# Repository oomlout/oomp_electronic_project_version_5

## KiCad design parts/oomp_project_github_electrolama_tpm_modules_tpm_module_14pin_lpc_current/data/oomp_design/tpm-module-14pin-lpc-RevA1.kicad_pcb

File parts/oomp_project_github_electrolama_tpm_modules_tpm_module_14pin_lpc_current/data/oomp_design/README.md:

# OOMP KiCad design copy

Open `tpm-module-14pin-lpc-RevA1.kicad_pro` (or the `.kicad_pcb` / `.kicad_sch`) in KiCad. Local OOMP libraries are under `libraries/`. Original inputs are preserved in [../original/](../original/).

Only verified unchanged installed KiCad defaults were renamed. Modified, custom, unmatched and unavailable items remain unchanged. Soldering variants are never swapped during conversion. Existing pad coordinates, nets and UUIDs are preserved.

See [conversion_report.yaml](conversion_report.yaml) for every conversion and skip. Copy this directory before editing; regeneration refuses to overwrite edited design files.

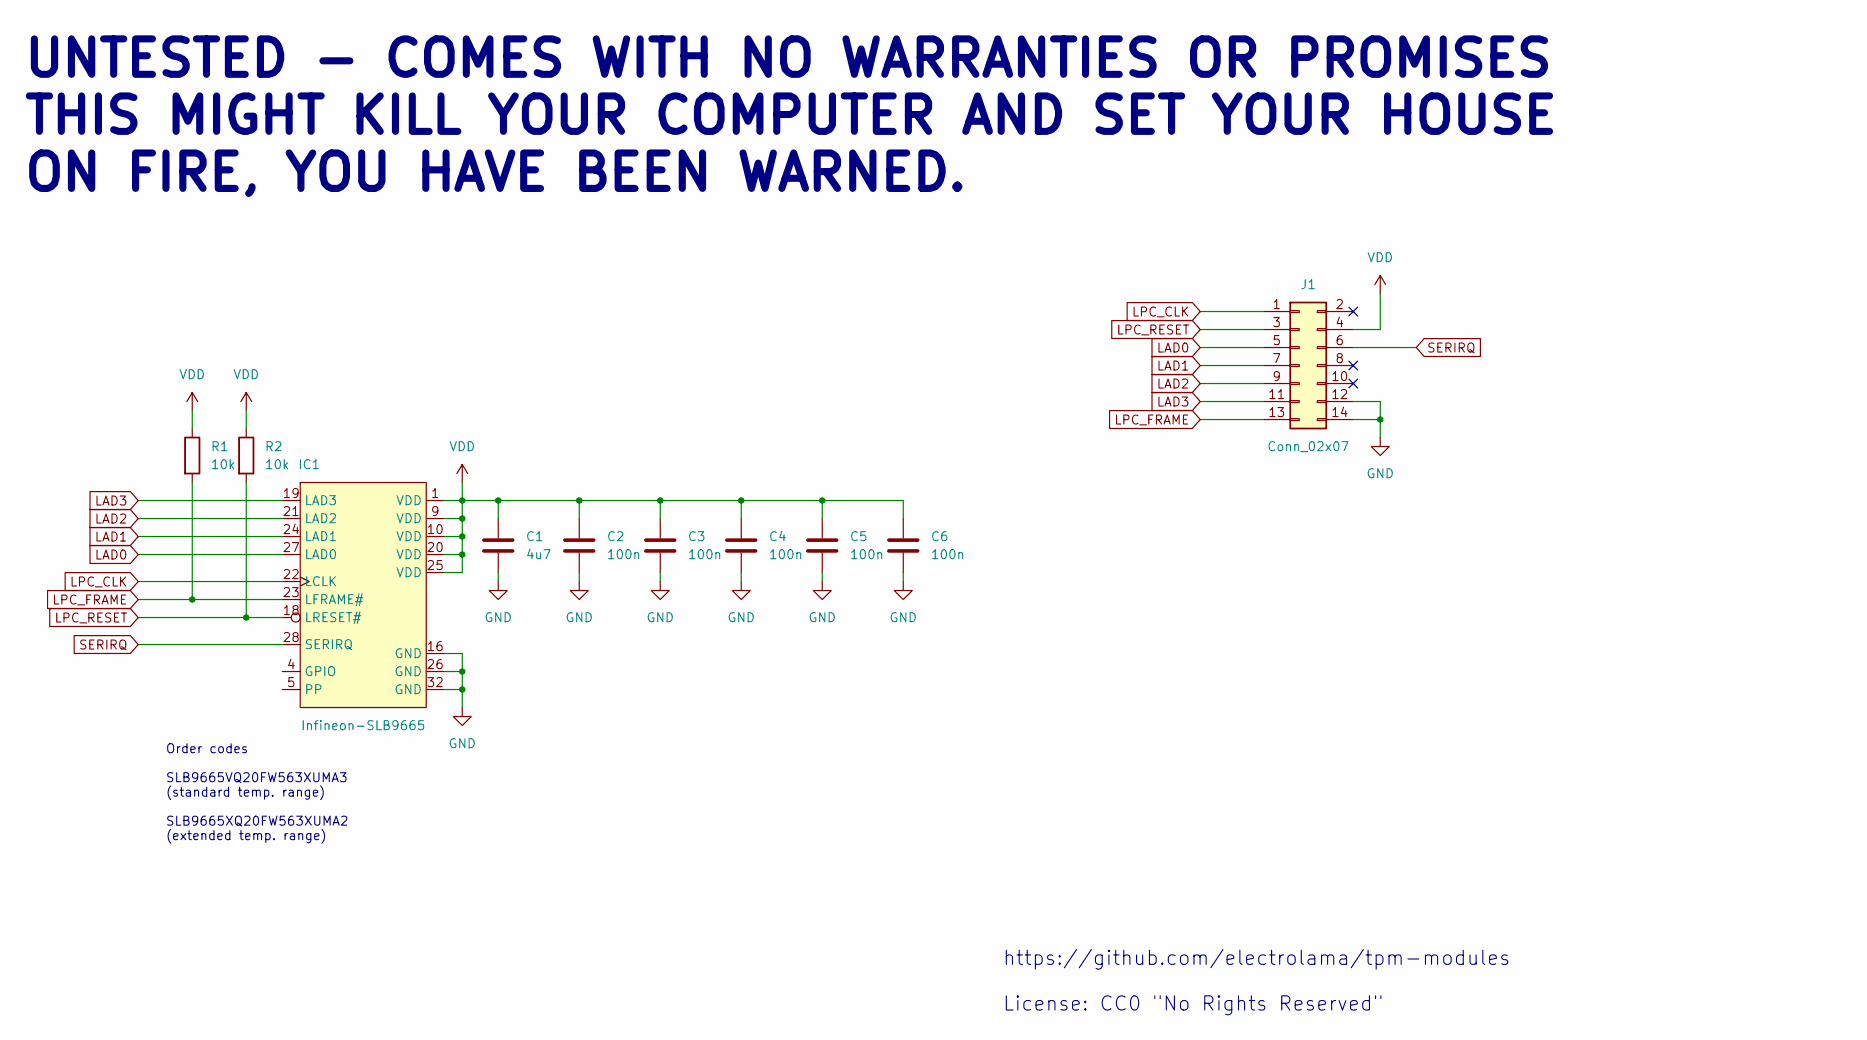
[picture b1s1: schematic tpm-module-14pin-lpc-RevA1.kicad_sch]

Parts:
C1: 4u7; C_0402_1005Metric
C2, C3, C4, C5, C6: 100n; C_0402_1005Metric
IC1: Infineon-SLB9665; QFN-32-1EP_5x5mm_P0.5mm_EP3.1x3.1mm
J1: Conn_02x07; PinSocket_2x07_P2.54mm_Horizontal
R1, R2: 10k; R_0402_1005Metric

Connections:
GND: C1.2, C2.2, C3.2, C4.2, C5.2, C6.2, IC1.16 (GND), IC1.26 (GND), IC1.32 (GND), J1.12, J1.14
LAD0: IC1.27 (LAD0), J1.5
LAD1: IC1.24 (LAD1), J1.7
LAD2: IC1.21 (LAD2), J1.9
LAD3: IC1.19 (LAD3), J1.11
LPC_CLK: IC1.22 (LCLK), J1.1
LPC_FRAME: IC1.23 (LFRAME#), J1.13, R1.2
LPC_RESET: IC1.18 (LRESET#), J1.3, R2.2
SERIRQ: IC1.28 (SERIRQ), J1.6
VDD: C1.1, C2.1, C3.1, C4.1, C5.1, C6.1, IC1.1 (VDD), IC1.9 (VDD), IC1.10 (VDD), IC1.20 (VDD), IC1.25 (VDD), J1.4, R1.1, R2.1

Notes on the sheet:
UNTESTED - COMES WITH NO WARRANTIES OR PROMISES THIS MIGHT KILL YOUR COMPUTER AND SET YOUR HOUSE ON FIRE, YOU HAVE BEEN WARNED.
Order codes SLB9665VQ20FW563XUMA3 (standard temp. range) SLB9665XQ20FW563XUMA2 (extended temp. range)
https://github.com/electrolama/tpm-modules License: CC0 "No Rights Reserved"

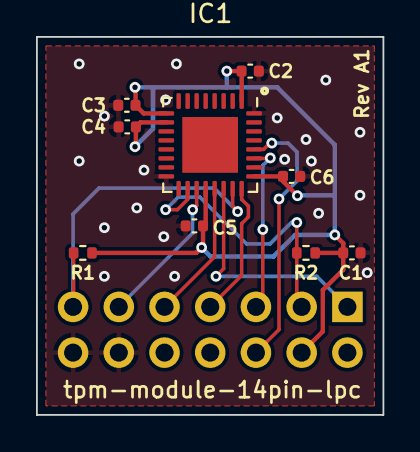
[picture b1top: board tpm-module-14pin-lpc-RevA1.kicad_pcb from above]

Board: 2 copper layers, 19.2 x 21.0 mm, 10 parts (1 on the bottom side), 10 nets.

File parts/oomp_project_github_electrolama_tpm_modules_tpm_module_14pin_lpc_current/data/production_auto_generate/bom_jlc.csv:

Comment,Designator,Footprint,LCSC Part #
100n,"C2,C3,C4,C5,C6",Capacitor_SMD:C_0402_1005Metric,C60474
10k,"R1,R2",Resistor_SMD:R_0402_1005Metric,C2906861
4u7,C1,Capacitor_SMD:C_0402_1005Metric,C368809
Conn_02x07,J1,Connector_PinSocket_2.54mm:PinSocket_2x07_P2.54mm_Horizontal,
Infineon-SLB9665,IC1,Package_DFN_QFN:QFN-32-1EP_5x5mm_P0.5mm_EP3.1x3.1mm,

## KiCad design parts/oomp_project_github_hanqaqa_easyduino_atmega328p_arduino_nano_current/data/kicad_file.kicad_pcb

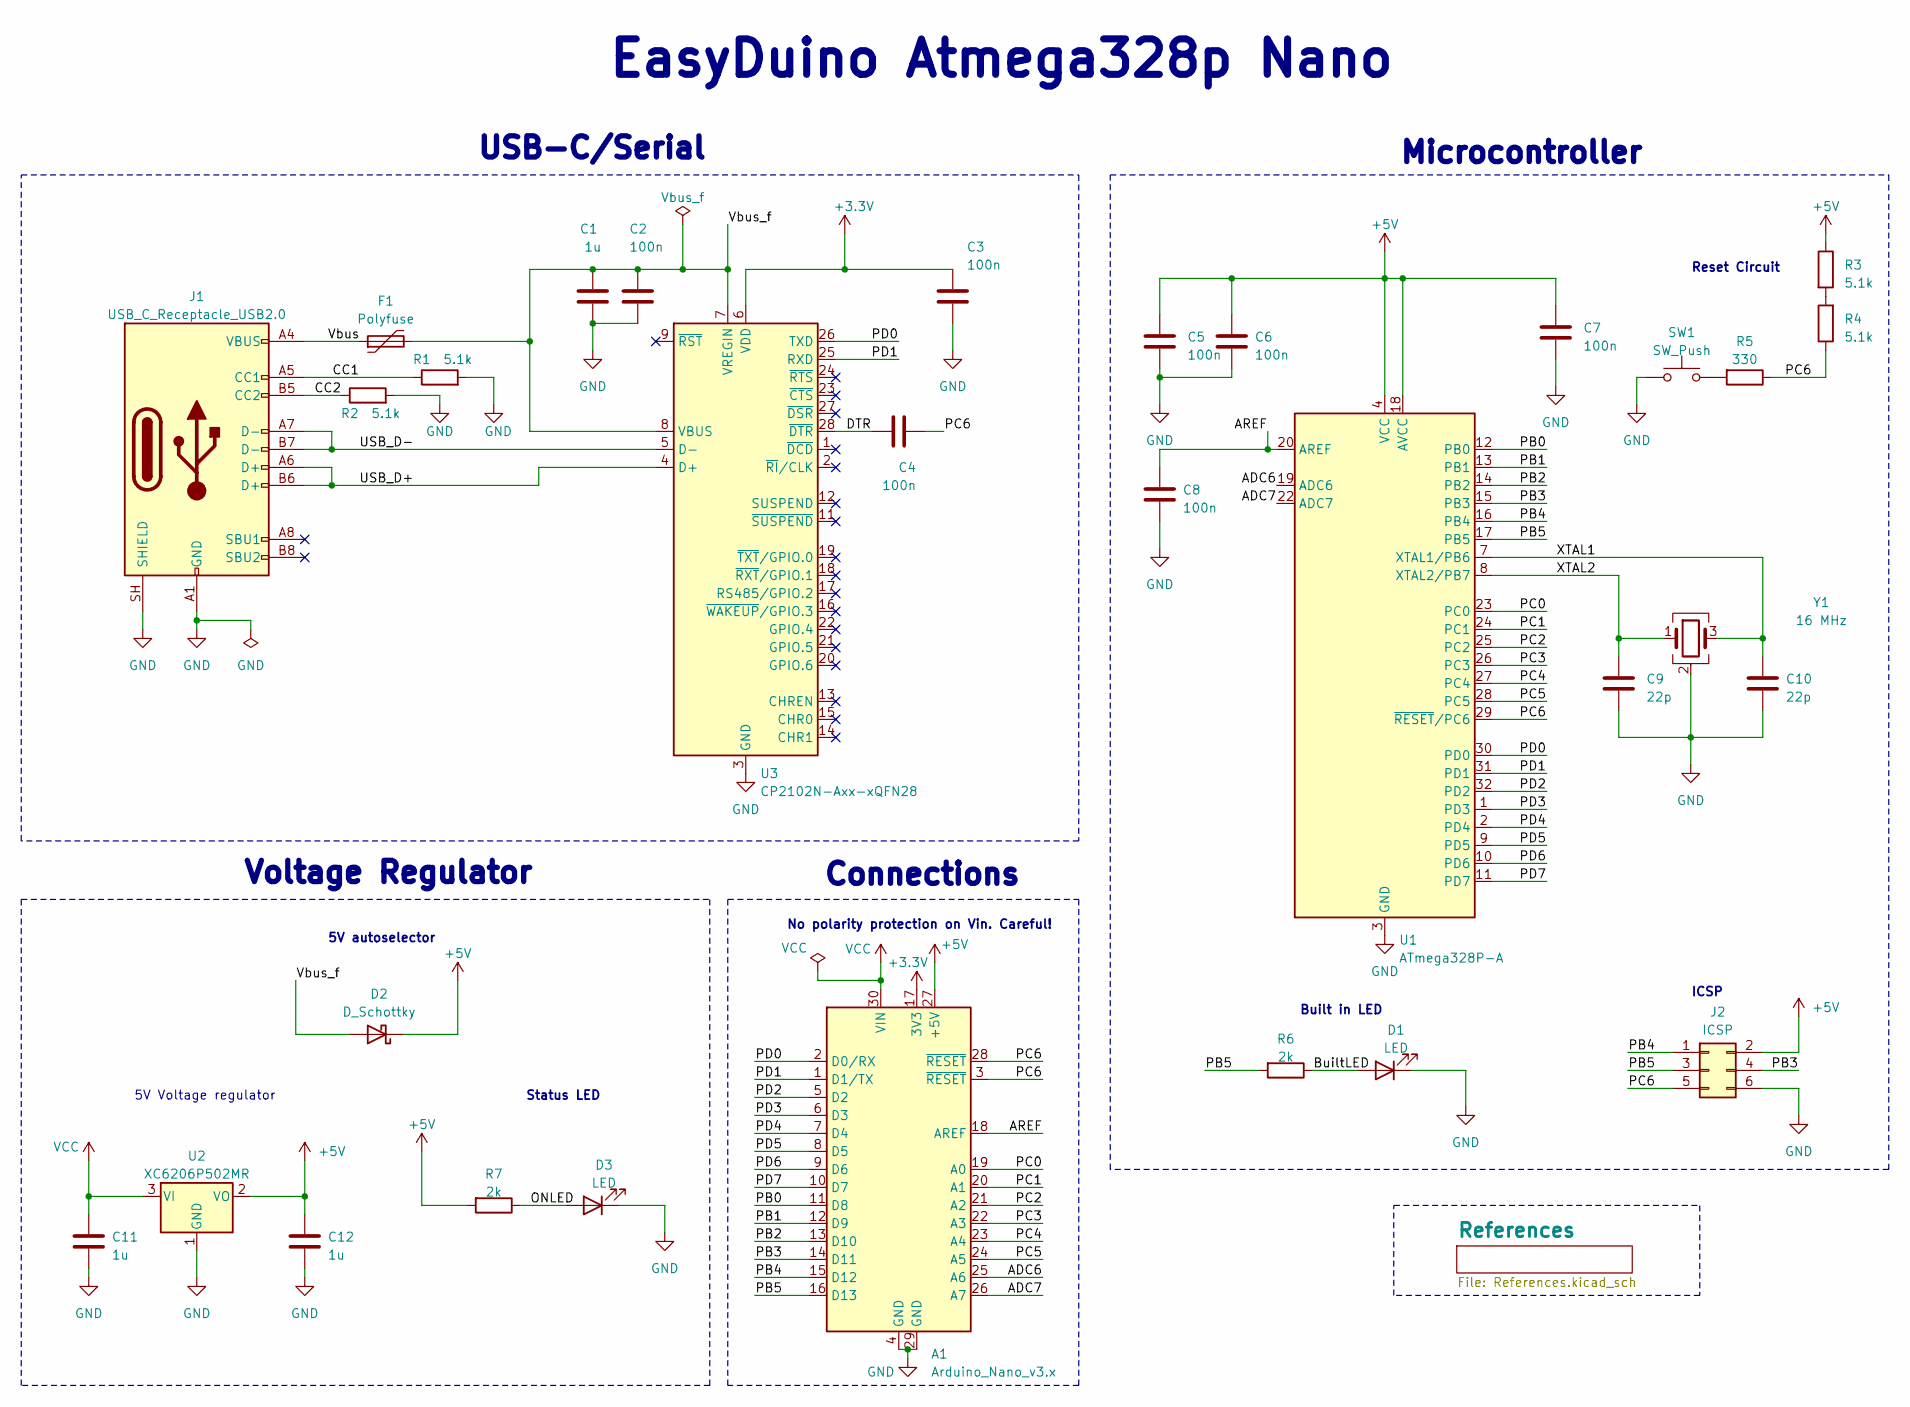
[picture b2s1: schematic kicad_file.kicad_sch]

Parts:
A1: Arduino_Nano_v3.x; Arduino_Nano_WithMountingHoles
C1, C11, C12: 1u; C_0402_1005Metric; LCSC C52923
C2, C3, C4, C5, C6, C7, C8: 100n; C_0402_1005Metric; LCSC C1525
C9, C10: 22p; C_0402_1005Metric; LCSC C1555
D1, D3: LED; LED_0402_1005Metric; LCSC C434447
D2: D_Schottky; D_0402_1005Metric; LCSC C2837790
F1: Polyfuse; Fuse_0402_1005Metric; LCSC C914087
J1: USB_C_Receptacle_USB2.0; USB_C_Receptacle_G-Switch_GT-USB-7010ASV; LCSC C2765186
J2: ICSP; PinHeader_2x03_P2.54mm_Vertical
R1, R2, R3, R4: 5.1k; R_0402_1005Metric; LCSC C25905
R5: 330; R_0402_1005Metric; LCSC C25104
R6, R7: 2k; R_0402_1005Metric; LCSC C4109
SW1: SW_Push; SW_Tactile_SPST_NO_Straight_CK_PTS636Sx25SMTRLFS; LCSC C520860
U1: ATmega328P-A; TQFP-32_7x7mm_P0.8mm; LCSC C14877
U2: XC6206P502MR; SOT-23-3; LCSC C16767
U3: CP2102N-Axx-xQFN28; QFN-28-1EP_5x5mm_P0.5mm_EP3.35x3.35mm; LCSC C6568
Y1: 16 MHz; Crystal_SMD_3225-4Pin_3.2x2.5mm; LCSC C13738

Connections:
+3.3V: A1.17 (3V3), C3.1, U3.6 (VDD)
+5V: A1.27 (+5V), C5.1, C6.1, C7.2, C12.1, D2.1 (K), J2.2, R3.1, R7.2, U1.4 (VCC), U1.6 (VCC), U1.18 (AVCC), U2.2 (VO)
/ADC6: A1.25 (A6), U1.19 (ADC6)
/ADC7: A1.26 (A7), U1.22 (ADC7)
/AREF: A1.18 (AREF), C8.1, U1.20 (AREF)
/BuiltLED: D1.2 (A), R6.1
/CC1: J1.A5 (CC1), R1.1
/CC2: J1.B5 (CC2), R2.1
/DTR: C4.1, U3.28 (~DTR)
/ONLED: D3.2 (A), R7.1
/PB0: A1.11 (D8), U1.12 (PB0)
/PB1: A1.12 (D9), U1.13 (PB1)
/PB2: A1.13 (D10), U1.14 (PB2)
/PB3: A1.14 (D11), J2.4, U1.15 (PB3)
/PB4: A1.15 (D12), J2.1, U1.16 (PB4)
/PB5: A1.16 (D13), J2.3, R6.2, U1.17 (PB5)
/PC0: A1.19 (A0), U1.23 (PC0)
/PC1: A1.20 (A1), U1.24 (PC1)
/PC2: A1.21 (A2), U1.25 (PC2)
/PC3: A1.22 (A3), U1.26 (PC3)
/PC4: A1.23 (A4), U1.27 (PC4)
/PC5: A1.24 (A5), U1.28 (PC5)
/PC6: A1.3 (~RESET), A1.28 (~RESET), C4.2, J2.5, R4.1, R5.1, U1.29 (~RESET/PC6)
/PD0: A1.2 (D0/RX), U1.30 (PD0), U3.26 (TXD)
/PD1: A1.1 (D1/TX), U1.31 (PD1), U3.25 (RXD)
/PD2: A1.5 (D2), U1.32 (PD2)
/PD3: A1.6 (D3), U1.1 (PD3)
/PD4: A1.7 (D4), U1.2 (PD4)
/PD5: A1.8 (D5), U1.9 (PD5)
/PD6: A1.9 (D6), U1.10 (PD6)
/PD7: A1.10 (D7), U1.11 (PD7)
/USB_D+: J1.A6 (D+), J1.B6 (D+), U3.4 (D+)
/USB_D-: J1.A7 (D-), J1.B7 (D-), U3.5 (D-)
/Vbus: F1.1, J1.A4 (VBUS), J1.A9 (VBUS), J1.B4 (VBUS), J1.B9 (VBUS)
/Vbus_f: C1.1, C2.1, D2.2 (A), F1.2, U3.7 (VREGIN), U3.8 (VBUS)
/XTAL1: C10.1, U1.7 (XTAL1/PB6), Y1.3
/XTAL2: C9.2, U1.8 (XTAL2/PB7), Y1.1
GND: A1.4 (GND), A1.29 (GND), C1.2, C2.2, C3.2, C5.2, C6.2, C7.1, C8.2, C9.1, C10.2, C11.2, C12.2, D1.1 (K), D3.1 (K), J1.A1 (GND), J1.A12 (GND), J1.B1 (GND), J1.B12 (GND), J1.SH (SHIELD), J2.6, R1.2, R2.2, SW1.1, U1.3 (GND), U1.5 (GND), U1.21 (GND), U2.1 (GND), U3.3 (GND), U3.29 (GND), Y1.2 (G), Y1.4 (G)
unnamed: R3.2, R4.2
unnamed: R5.2, SW1.2
VCC: A1.30 (VIN), C11.1, U2.3 (VI)

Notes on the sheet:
USB-C/Serial
Status LED
Microcontroller
Connections
ICSP
Reset Circuit
Voltage Regulator
5V autoselector
EasyDuino Atmega328p Nano
Built in LED
No polarity protection on Vin. Careful!
5V Voltage regulator

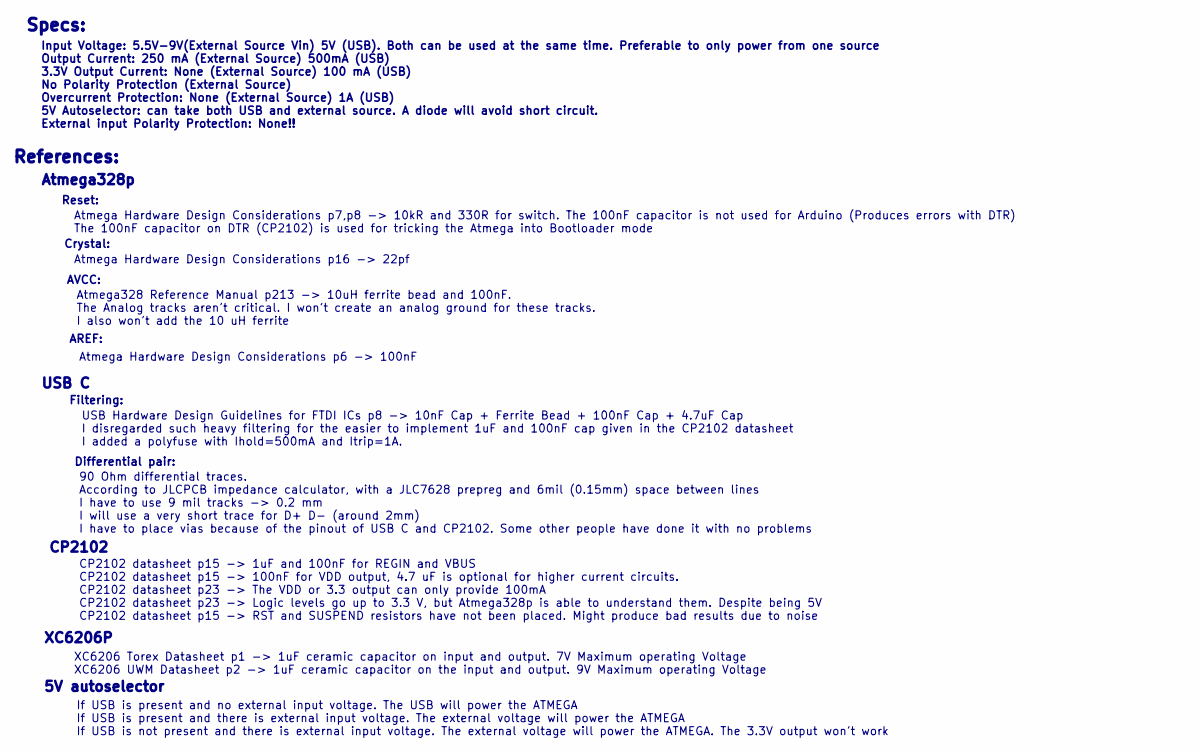
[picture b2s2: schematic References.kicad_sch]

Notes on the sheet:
AREF:
References:
Atmega328 Reference Manual p213 -> 10uH ferrite bead and 100nF. The Analog tracks aren't critical. I won't create an analog ground for these tracks. I also won't add the 10 uH ferrite
Atmega Hardware Design Considerations p7,p8 -> 10kR and 330R for switch. The 100nF capacitor is not used for Arduino (Produces errors with DTR) The 100nF capacitor on DTR (CP2102) is used for tricking the Atmega into Bootloader mode
Atmega328p
Specs:
CP2102
90 Ohm differential traces. According to JLCPCB impedance calculator, with a JLC7628 prepreg and 6mil (0.15mm) space between lines I have to use 9 mil tracks -> 0.2 mm I will use a very short trace for D+ D- (around 2mm) I have to place vias because of the pinout of USB C and CP2102. Some other peo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
5V autoselector
Filtering:
If USB is present and no external input voltage. The USB will power the ATMEGA If USB is present and there is external input voltage. The external voltage will power the ATMEGA If USB is not present and there is external input voltage. The external voltage will power the ATMEGA. The 3.3V output won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
XC6206P
Crystal:
Reset:
CP2102 datasheet p15 -> 1uF and 100nF for REGIN and VBUS CP2102 datasheet p15 -> 100nF for VDD output, 4.7 uF is optional for higher current circuits. CP2102 datasheet p23 -> The VDD or 3.3 output can only provide 100mA CP2102 datasheet p23 -> Logic levels go up to 3.3 V, but Atmega328p is able to 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
AVCC:
Atmega Hardware Design Considerations p6 -> 100nF
USB C
Differential pair:
USB Hardware Design Guidelines for FTDI ICs p8 -> 10nF Cap + Ferrite Bead + 100nF Cap + 4.7uF Cap I disregarded such heavy filtering for the easier to implement 1uF and 100nF cap given in the CP2102 datasheet I added a polyfuse with Ihold=500mA and Itrip=1A.
Atmega Hardware Design Considerations p16 -> 22pf
Input Voltage: 5.5V-9V(External Source Vin) 5V (USB). Both can be used at the same time. Preferable to only power from one source Output Current: 250 mA (External Source) 500mA (USB) 3.3V Output Current: None (External Source) 100 mA (USB) No Polarity Protection (External Source) Overcurrent Protec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
XC6206 Torex Datasheet p1 -> 1uF ceramic capacitor on input and output. 7V Maximum operating Voltage XC6206 UWM Datasheet p2 -> 1uF ceramic capacitor on the input and output. 9V Maximum operating Voltage

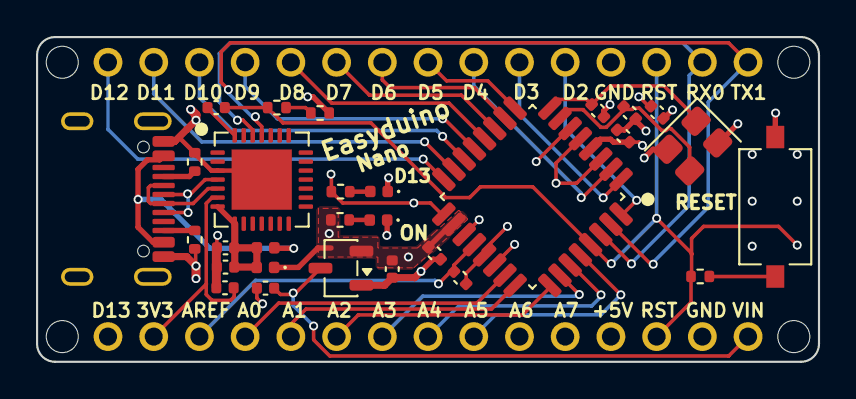
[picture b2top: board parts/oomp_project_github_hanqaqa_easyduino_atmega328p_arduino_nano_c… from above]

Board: 4 copper layers, 43.4 x 18.0 mm, 31 parts (1 on the bottom side), 41 nets.

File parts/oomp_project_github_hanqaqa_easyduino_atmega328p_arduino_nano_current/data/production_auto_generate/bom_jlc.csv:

Comment,Designator,Footprint,LCSC Part #
100n,"C2,C3,C4,C5,C6,C7,C8",Capacitor_SMD:C_0402_1005Metric,C1525
16 MHz,Y1,Crystal:Crystal_SMD_3225-4Pin_3.2x2.5mm,C13738
1u,"C1,C11,C12",Capacitor_SMD:C_0402_1005Metric,C52923
22p,"C9,C10",Capacitor_SMD:C_0402_1005Metric,C1555
2k,"R6,R7",Resistor_SMD:R_0402_1005Metric,C4109
330,R5,Resistor_SMD:R_0402_1005Metric,C25104
5.1k,"R1,R2,R3,R4",Resistor_SMD:R_0402_1005Metric,C25905
Arduino_Nano_v3.x,A1,Module:Arduino_Nano_WithMountingHoles,-
ATmega328P-A,U1,Package_QFP:TQFP-32_7x7mm_P0.8mm,C14877
CP2102N-Axx-xQFN28,U3,Package_DFN_QFN:QFN-28-1EP_5x5mm_P0.5mm_EP3.35x3.35mm,C6568
D_Schottky,D2,Diode_SMD:D_0402_1005Metric,C2837790
ICSP,J2,Connector_PinHeader_2.54mm:PinHeader_2x03_P2.54mm_Vertical,-
LED,"D1,D3",LED_SMD:LED_0402_1005Metric,C434447
Polyfuse,F1,Fuse:Fuse_0402_1005Metric,C914087
SW_Push,SW1,Button_Switch_SMD:SW_Tactile_SPST_NO_Straight_CK_PTS636Sx25SMTRLFS,C520860
USB_C_Receptacle_USB2.0,J1,Connector_USB:USB_C_Receptacle_G-Switch_GT-USB-7010ASV,C2765186
XC6206P502MR,U2,Package_TO_SOT_SMD:SOT-23-3,C16767

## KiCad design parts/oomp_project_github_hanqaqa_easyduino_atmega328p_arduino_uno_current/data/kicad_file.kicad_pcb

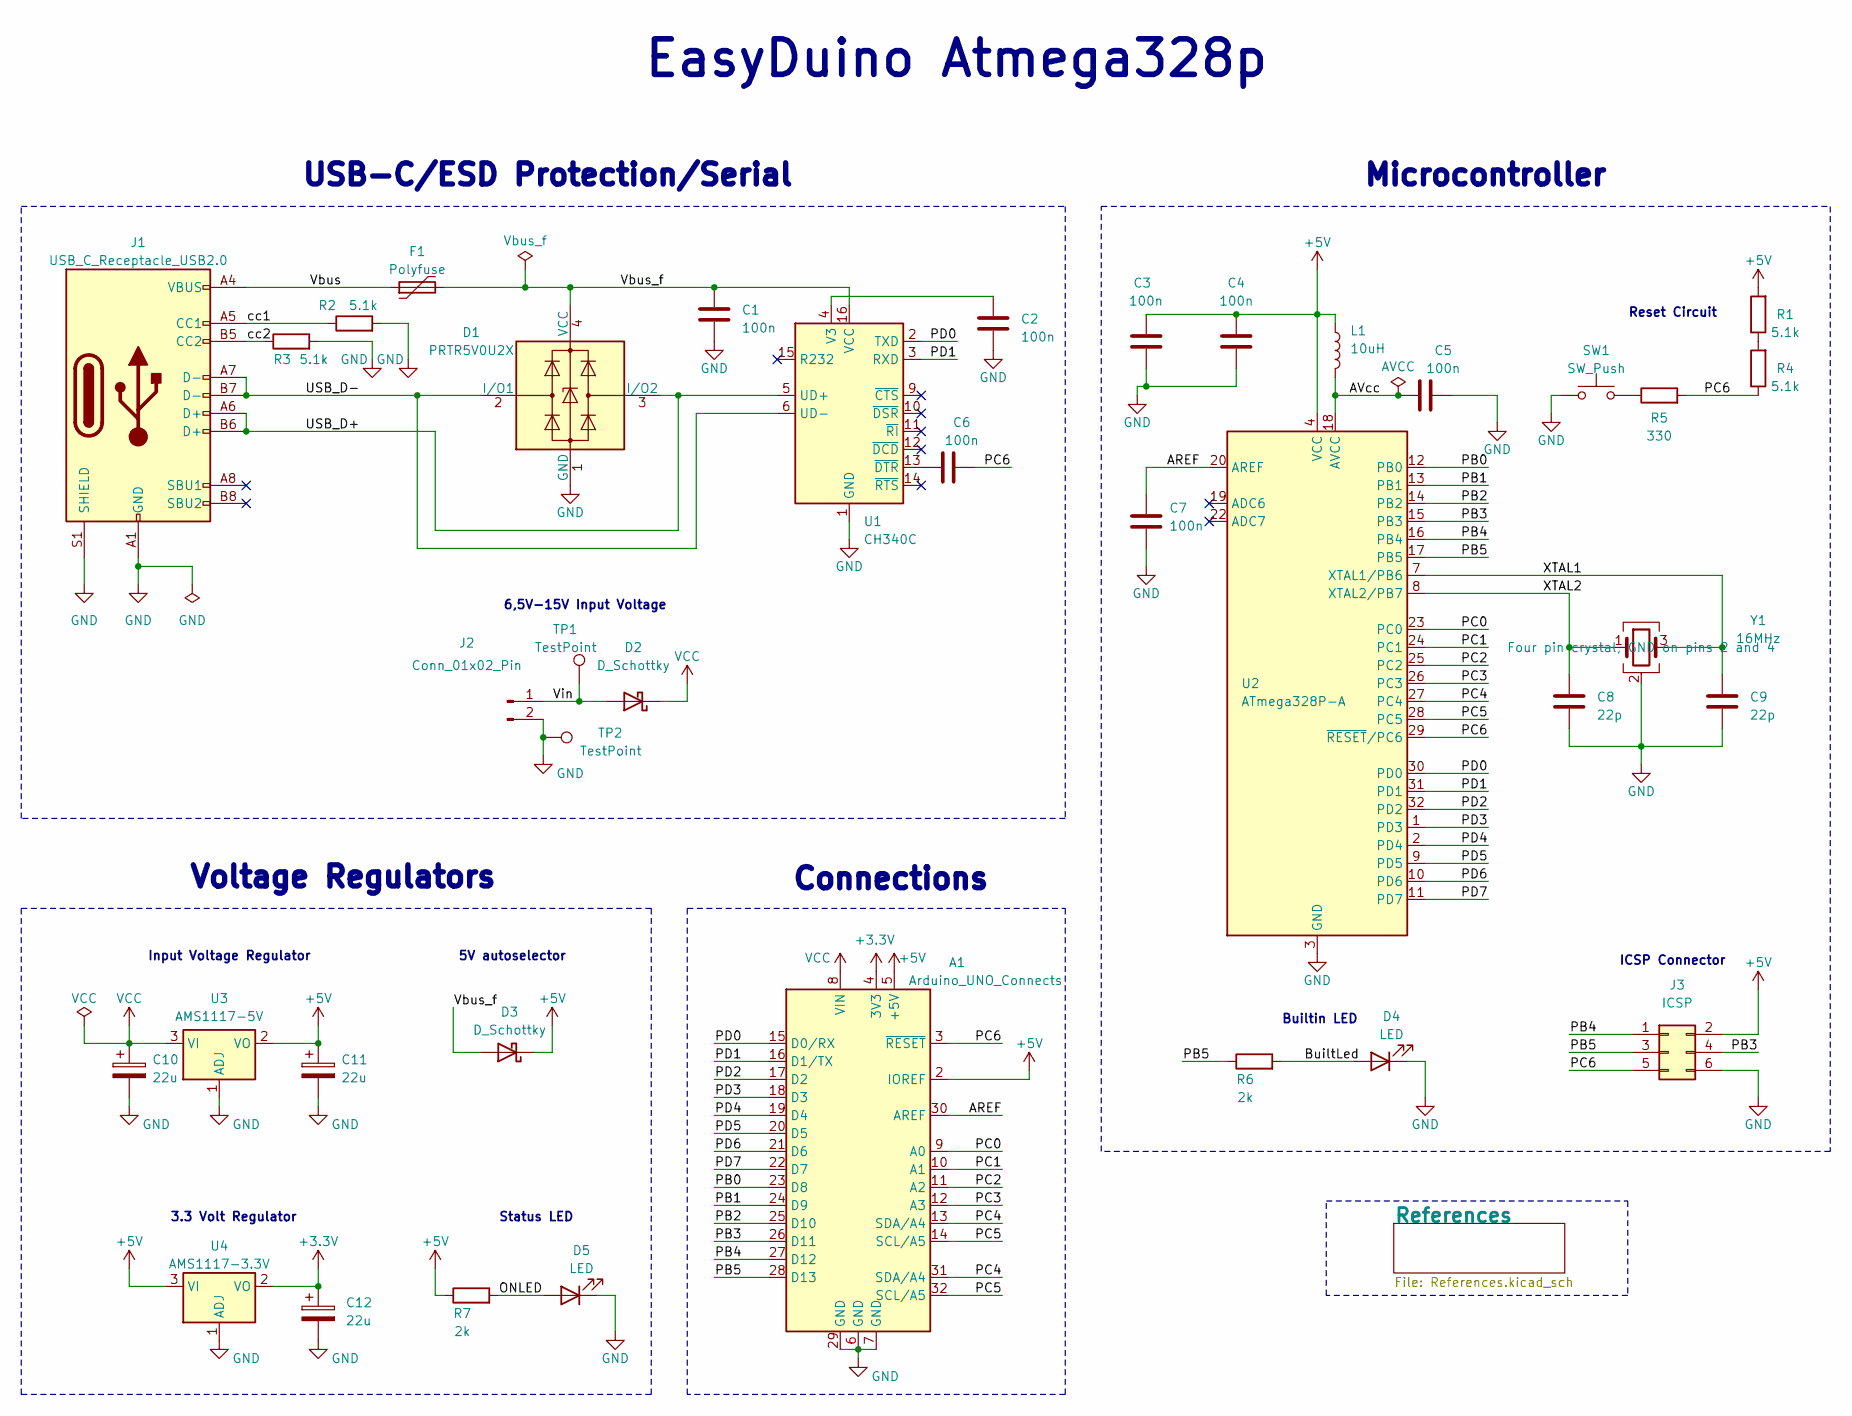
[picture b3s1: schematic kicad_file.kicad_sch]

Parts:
A1: Arduino_UNO_Connects; Arduino_UNO_R3_WithMountingHoles
C1, C2, C3, C4, C5, C6, C7: 100n; C_0603_1608Metric; LCSC C14663
C8, C9: 22p; C_0603_1608Metric; LCSC C1653
C10, C11, C12: 22u; CP_EIA-3216-10_Kemet-I; LCSC C11366
D1: PRTR5V0U2X; SOT-143; LCSC C2827688
D2, D3: D_Schottky; D_SOD-123; LCSC C8598
D4, D5: LED; D_0603_1608Metric; LCSC C72043
F1: Polyfuse; Fuse_1206_3216Metric; LCSC C70077
J1: USB_C_Receptacle_USB2.0; USB_C_Receptacle_G-Switch_GT-USB-7010ASV; LCSC C2765186
J2: Conn_01x02_Pin; PinHeader_1x02_P2.54mm_Vertical
J3: ICSP; PinHeader_2x03_P2.54mm_Vertical
L1: 10uH; L_0603_1608Metric; LCSC C51942
R1, R2, R3, R4: 5.1k; R_0603_1608Metric; LCSC C23186
R5: 330; R_0603_1608Metric; LCSC C23138
R6, R7: 2k; R_0603_1608Metric; LCSC C22940
SW1: SW_Push; SW_SPST_Omron_B3FS-100xP; LCSC C271751
TP1, TP2: TestPoint; TestPoint_Pad_2.5x2.5mm
U1: CH340C; SOIC-16_3.9x9.9mm_P1.27mm; LCSC C84681
U2: ATmega328P-A; TQFP-32_7x7mm_P0.8mm; LCSC C14877
U3: AMS1117-5V; SOT-223-3_TabPin2; LCSC C6187
U4: AMS1117-3.3V; SOT-223-3_TabPin2; LCSC C6186
Y1: 16MHz; Crystal_SMD_3225-4Pin_3.2x2.5mm; LCSC C13738

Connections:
+3.3V: A1.4 (3V3), C12.1, U4.2 (VO)
+5V: A1.2 (IOREF), A1.5 (+5V), C3.2, C4.2, C11.1, D3.1 (K), J3.2, L1.1, R1.2, R7.1, U2.4 (VCC), U2.6 (VCC), U3.2 (VO), U4.3 (VI)
/AREF: A1.30 (AREF), C7.1, U2.20 (AREF)
/AVcc: C5.1, L1.2, U2.18 (AVCC)
/BuiltLed: D4.2 (A), R6.2
/ONLED: D5.2 (A), R7.2
/PB0: A1.23 (D8), U2.12 (PB0)
/PB1: A1.24 (D9), U2.13 (PB1)
/PB2: A1.25 (D10), U2.14 (PB2)
/PB3: A1.26 (D11), J3.4, U2.15 (PB3)
/PB4: A1.27 (D12), J3.1, U2.16 (PB4)
/PB5: A1.28 (D13), J3.3, R6.1, U2.17 (PB5)
/PC0: A1.9 (A0), U2.23 (PC0)
/PC1: A1.10 (A1), U2.24 (PC1)
/PC2: A1.11 (A2), U2.25 (PC2)
/PC3: A1.12 (A3), U2.26 (PC3)
/PC4: A1.13 (SDA/A4), A1.31 (SDA/A4), U2.27 (PC4)
/PC5: A1.14 (SCL/A5), A1.32 (SCL/A5), U2.28 (PC5)
/PC6: A1.3 (~RESET), C6.2, J3.5, R4.1, R5.2, U2.29 (~RESET/PC6)
/PD0: A1.15 (D0/RX), U1.2 (TXD), U2.30 (PD0)
/PD1: A1.16 (D1/TX), U1.3 (RXD), U2.31 (PD1)
/PD2: A1.17 (D2), U2.32 (PD2)
/PD3: A1.18 (D3), U2.1 (PD3)
/PD4: A1.19 (D4), U2.2 (PD4)
/PD5: A1.20 (D5), U2.9 (PD5)
/PD6: A1.21 (D6), U2.10 (PD6)
/PD7: A1.22 (D7), U2.11 (PD7)
/USB_D+: D1.3 (I/O2), J1.A6 (D+), J1.B6 (D+), U1.5 (UD+)
/USB_D-: D1.2 (I/O1), J1.A7 (D-), J1.B7 (D-), U1.6 (UD-)
/Vbus: F1.1, J1.A4 (VBUS), J1.A9 (VBUS), J1.B4 (VBUS), J1.B9 (VBUS)
/Vbus_f: C1.1, D1.4 (VCC), D3.2 (A), F1.2, U1.16 (VCC)
/Vin: D2.2 (A), J2.1, TP1.1 (1_1)
/XTAL1: C9.2, U2.7 (XTAL1/PB6), Y1.3
/XTAL2: C8.2, U2.8 (XTAL2/PB7), Y1.1
/cc1: J1.A5 (CC1), R2.1
/cc2: J1.B5 (CC2), R3.1
GND: A1.6 (GND), A1.7 (GND), A1.29 (GND), C1.2, C2.2, C3.1, C4.1, C5.2, C7.2, C8.1, C9.1, C10.2, C11.2, C12.2, D1.1 (GND), D4.1 (K), D5.1 (K), J1.A1 (GND), J1.A12 (GND), J1.B1 (GND), J1.B12 (GND), J1.S1 (SHIELD), J2.2, J3.6, R2.2, R3.2, SW1.1, TP2.1 (1_1), U1.1 (GND), U2.3 (GND), U2.5 (GND), U2.21 (GND), U3.1 (ADJ), U4.1 (ADJ), Y1.2 (G), Y1.4 (G)
unnamed: R1.1, R4.2
unnamed: R5.1, SW1.2
unnamed: C2.1, U1.4 (V3)
unnamed: C6.1, U1.13 (~DTR)
VCC: A1.8 (VIN), C10.1, D2.1 (K), U3.3 (VI)

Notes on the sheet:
Status LED
Connections
Voltage Regulators
ICSP Connector
Microcontroller
5V autoselector
USB-C/ESD Protection/Serial
Builtin LED
EasyDuino Atmega328p
Reset Circuit
6,5V-15V Input Voltage
3.3 Volt Regulator
Input Voltage Regulator

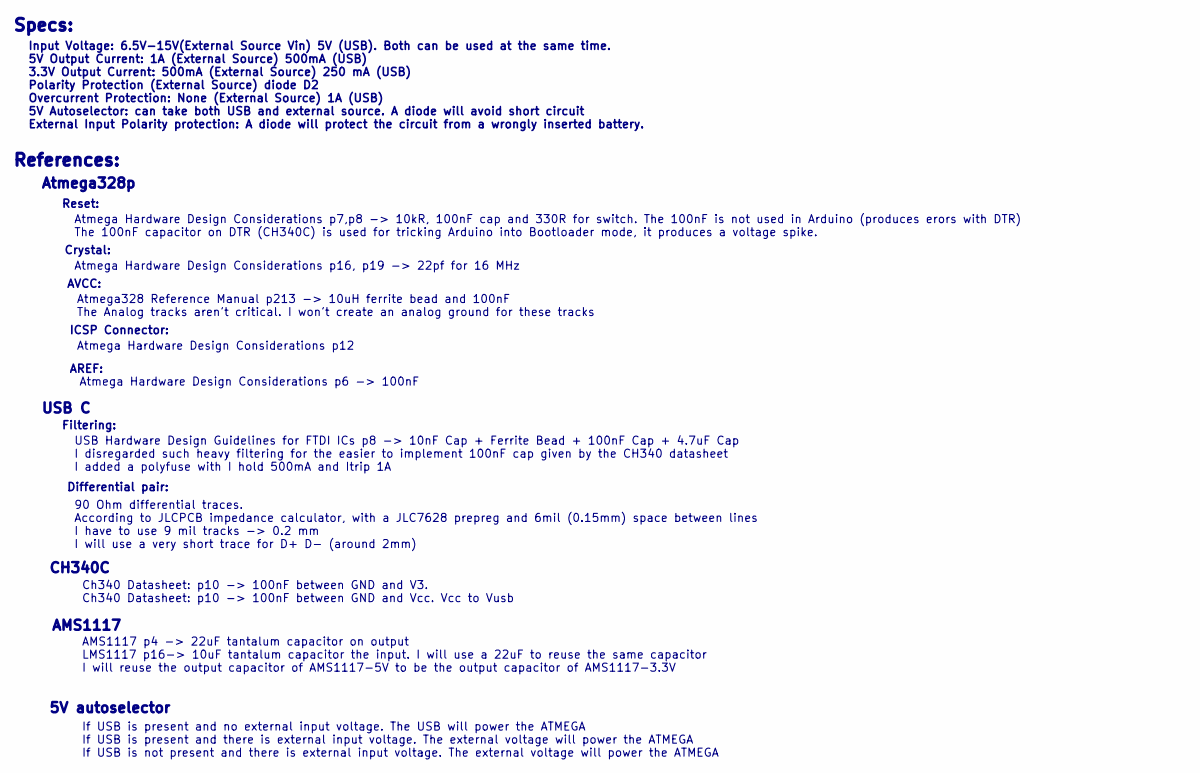
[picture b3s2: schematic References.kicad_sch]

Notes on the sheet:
Specs:
Atmega328p
90 Ohm differential traces. According to JLCPCB impedance calculator, with a JLC7628 prepreg and 6mil (0.15mm) space between lines I have to use 9 mil tracks -> 0.2 mm I will use a very short trace for D+ D- (around 2mm)
CH340C
Atmega328 Reference Manual p213 -> 10uH ferrite bead and 100nF The Analog tracks aren't critical. I won't create an analog ground for these tracks
Filtering:
Atmega Hardware Design Considerations p12
AMS1117
ICSP Connector:
References:
If USB is present and no external input voltage. The USB will power the ATMEGA If USB is present and there is external input voltage. The external voltage will power the ATMEGA If USB is not present and there is external input voltage. The external voltage will power the ATMEGA
AVCC:
USB Hardware Design Guidelines for FTDI ICs p8 -> 10nF Cap + Ferrite Bead + 100nF Cap + 4.7uF Cap I disregarded such heavy filtering for the easier to implement 100nF cap given by the CH340 datasheet I added a polyfuse with I hold 500mA and Itrip 1A
Reset:
Differential pair:
Crystal:
USB C
Atmega Hardware Design Considerations p6 -> 100nF
5V autoselector
Ch340 Datasheet: p10 -> 100nF between GND and V3. Ch340 Datasheet: p10 -> 100nF between GND and Vcc. Vcc to Vusb
Atmega Hardware Design Considerations p7,p8 -> 10kR, 100nF cap and 330R for switch. The 100nF is not used in Arduino (produces erors with DTR) The 100nF capacitor on DTR (CH340C) is used for tricking Arduino into Bootloader mode, it produces a voltage spike.
AREF:
AMS1117 p4 -> 22uF tantalum capacitor on output LMS1117 p16-> 10uF tantalum capacitor the input. I will use a 22uF to reuse the same capacitor I will reuse the output capacitor of AMS1117-5V to be the output capacitor of AMS1117-3.3V
Input Voltage: 6.5V-15V(External Source Vin) 5V (USB). Both can be used at the same time. 5V Output Current: 1A (External Source) 500mA (USB) 3.3V Output Current: 500mA (External Source) 250 mA (USB) Polarity Protection (External Source) diode D2 Overcurrent Protection: None (External Source) 1A (U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
Atmega Hardware Design Considerations p16, p19 -> 22pf for 16 MHz

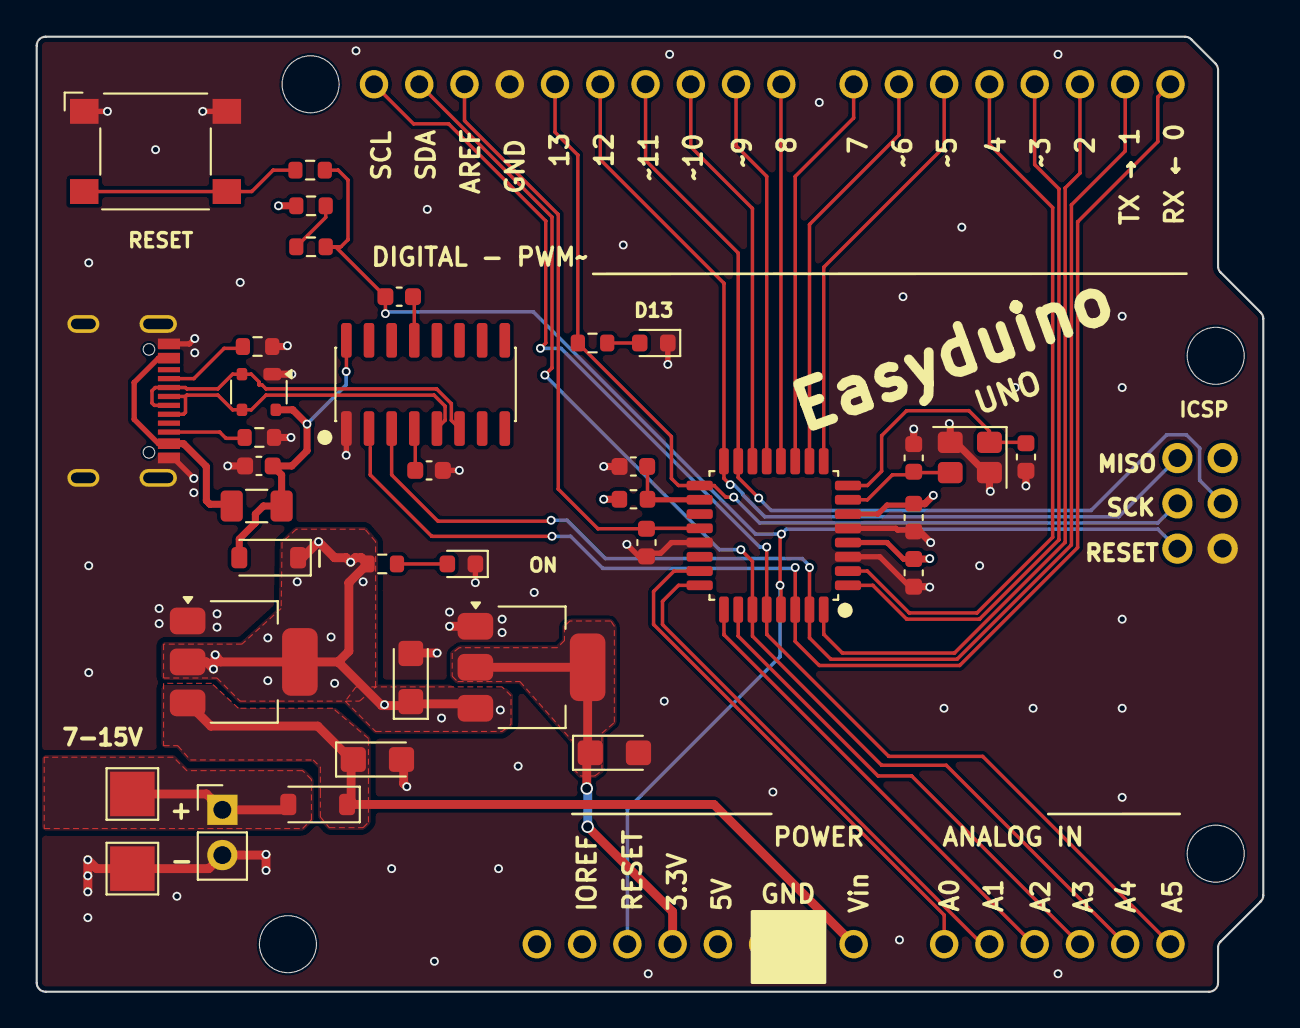
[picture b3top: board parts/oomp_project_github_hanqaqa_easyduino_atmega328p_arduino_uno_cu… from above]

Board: 4 copper layers, 68.8 x 53.6 mm, 38 parts (1 on the bottom side), 42 nets.

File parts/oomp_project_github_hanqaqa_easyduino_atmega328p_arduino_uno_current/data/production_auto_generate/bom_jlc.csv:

Comment,Designator,Footprint,LCSC Part #
100n,"C1,C2,C3,C4,C5,C6,C7",Capacitor_SMD:C_0603_1608Metric,C14663
10uH,L1,Inductor_SMD:L_0603_1608Metric,C51942
16MHz,Y1,Crystal:Crystal_SMD_3225-4Pin_3.2x2.5mm,C13738
22p,"C8,C9",Capacitor_SMD:C_0603_1608Metric,C1653
22u,"C10,C11,C12",Capacitor_Tantalum_SMD:CP_EIA-3216-10_Kemet-I,C11366
2k,"R6,R7",Resistor_SMD:R_0603_1608Metric,C22940
330,R5,Resistor_SMD:R_0603_1608Metric,C23138
5.1k,"R1,R2,R3,R4",Resistor_SMD:R_0603_1608Metric,C23186
AMS1117-3.3V,U4,Package_TO_SOT_SMD:SOT-223-3_TabPin2,C6186
AMS1117-5V,U3,Package_TO_SOT_SMD:SOT-223-3_TabPin2,C6187
Arduino_UNO_Connects,A1,Module:Arduino_UNO_R3_WithMountingHoles,-
ATmega328P-A,U2,Package_QFP:TQFP-32_7x7mm_P0.8mm,C14877
CH340C,U1,Package_SO:SOIC-16_3.9x9.9mm_P1.27mm,C84681
Conn_01x02_Pin,J2,Connector_PinHeader_2.54mm:PinHeader_1x02_P2.54mm_Vertical,-
D_Schottky,"D2,D3",Diode_SMD:D_SOD-123,C8598
ICSP,J3,Connector_PinHeader_2.54mm:PinHeader_2x03_P2.54mm_Vertical,-
LED,"D4,D5",Diode_SMD:D_0603_1608Metric,C72043
Polyfuse,F1,Fuse:Fuse_1206_3216Metric,C70077
PRTR5V0U2X,D1,Package_TO_SOT_SMD:SOT-143,C2827688
SW_Push,SW1,Button_Switch_SMD:SW_SPST_Omron_B3FS-100xP,C271751
TestPoint,"TP1,TP2",TestPoint:TestPoint_Pad_2.5x2.5mm,-
USB_C_Receptacle_USB2.0,J1,Connector_USB:USB_C_Receptacle_G-Switch_GT-USB-7010ASV,C2765186
